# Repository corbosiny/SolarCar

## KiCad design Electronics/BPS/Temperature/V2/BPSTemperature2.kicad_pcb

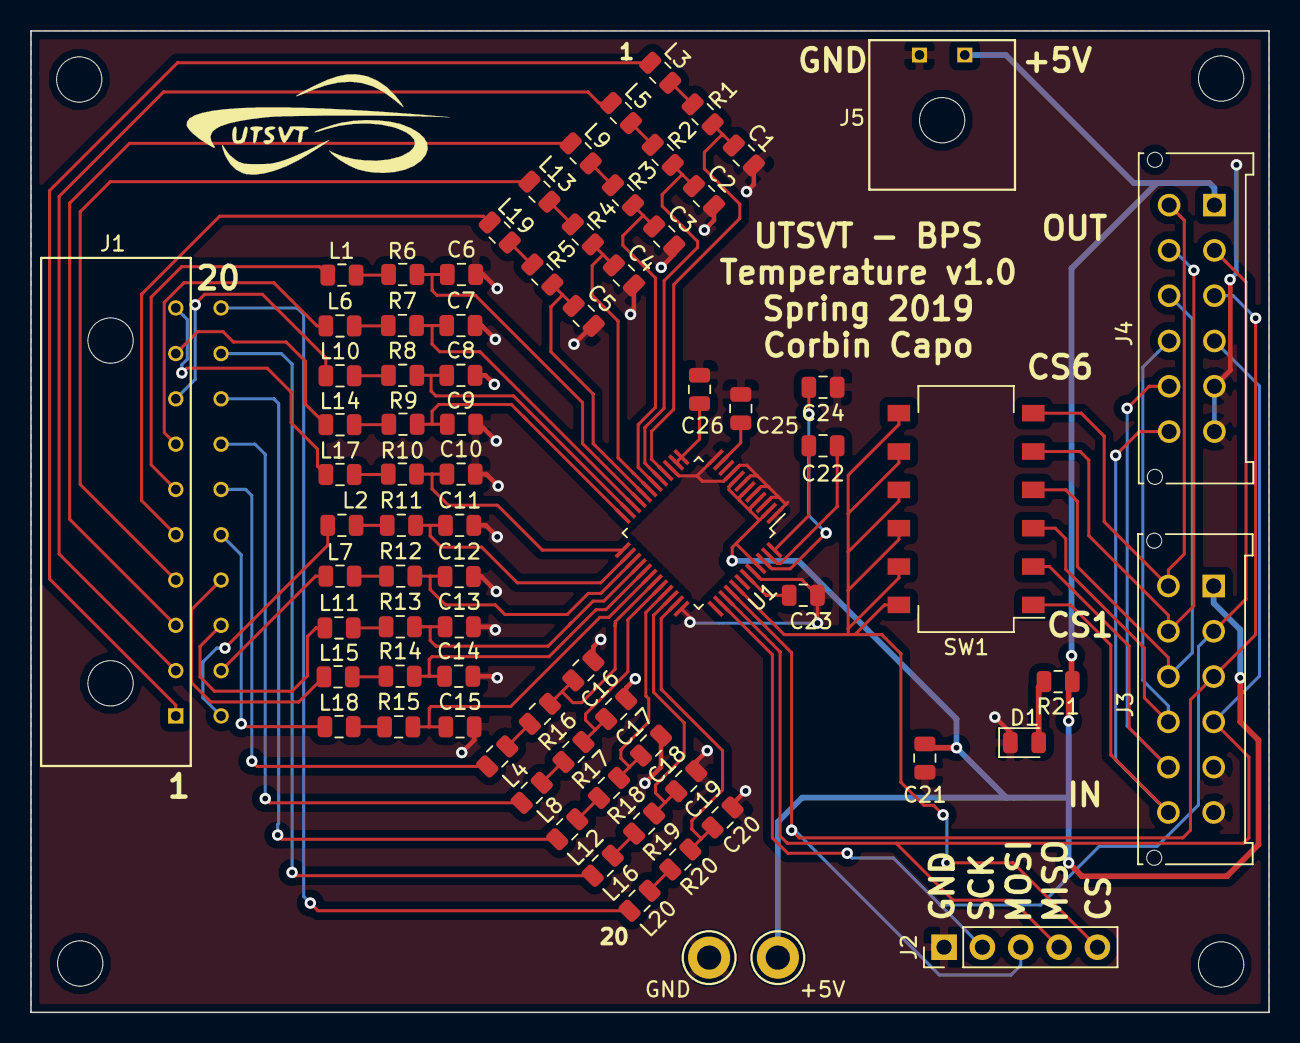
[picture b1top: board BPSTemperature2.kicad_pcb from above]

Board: 2 copper layers, 82.0 x 65.0 mm, 81 parts (0 on the bottom side), 79 nets.

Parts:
+5V: TestPoint; TestPoint_Keystone_5005-5009_Compact
C1, C2, C3, C4, C5, C6, C7, C8, C9, C10, C11, C12, C13, C14, C15, C16, C17, C18, C19, C20, C25, C26: 1uF; C_0805_2012Metric
C21: 0.1uF; C_0805_2012Metric
C22, C23, C24: 10uF; C_0805_2012Metric
D1: LED; LED_0805_2012Metric
GND: TestPoint; TestPoint_Keystone_5005-5009_Compact
J1: Conn_02x10_Counter_Clockwise; 02x10_Microfit_3.0_horizontal
J2: Logic Analyzer; PinHeader_1x05_P2.54mm_Vertical
J3, J4: Conn_02x06_Counter_Clockwise; Molex_MicroFit3.0_2x6xP3.00mm_PolarizingPeg_Vertical
J5: Conn_01x02; 43650-0202_01x02_Microfit 3.0_horizontal
L1, L2, L3, L4, L5, L6, L7, L8, L9, L10, L11, L12, L13, L14, L15, L16, L17, L18, L19, L20: Ferrite_Bead; L_0805_2012Metric
MH1, MH2, MH3, MH4: MountingHole; MountingHole_3mm
R1, R2, R3, R4, R5, R6, R7, R8, R9, R10, R11, R12, R13, R14, R15, R16, R17, R18, R19, R20: 1k; R_0805_2012Metric
R21: 1.55k; R_0805_2012Metric
SW1: SW_DIP_x06; SW_DIP_SPSTx06_Slide_Omron_A6S-610x_W8.9mm_P2.54mm
U1: LTC2983; LQFP-48_7x7mm_P0.5mm

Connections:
+5V: +5V.1, C21.2, J3.1, J4.1, J5.1, R21.1, U1.2, U1.4, U1.6, U1.8, U1.45
/CH1_LPF: J1.1, L3.2
/CH2_LPF: J1.2, L5.2
/CH3_LPF: J1.3, L9.2
/CH4_LPF: J1.4, L13.2
/CH5_LPF: J1.5, L19.2
/CH6_LPF: J1.6, L1.1
/CH7_LPF: J1.7, L6.1
/CH8_LPF: J1.8, L10.1
/CH9_LPF: J1.9, L14.1
/CH10_LPF: J1.10, L17.2
/CH11_LPF: J1.11, L2.1
/CH12_LPF: J1.12, L7.1
/CH13_LPF: J1.13, L11.1
/CH14_LPF: J1.14, L15.1
/CH15_LPF: J1.15, L18.1
/CH16_LPF: J1.16, L4.1
/CH17_LPF: J1.17, L8.1
/CH18_LPF: J1.18, L12.1
/CH19_LPF: J1.19, L16.1
/CH20_LPF: J1.20, L20.1
/CS1: J3.12, J4.12, SW1.1
/CS1_OUT: J2.5, SW1.7, SW1.8, SW1.9, SW1.10, SW1.11, SW1.12, U1.41
/CS2: J3.11, J4.11, SW1.2
/CS3: J3.10, J4.10, SW1.3
/CS4: J3.9, J4.9, SW1.4
/CS5: J3.8, J4.8, SW1.5
/CS6: J3.7, J4.7, SW1.6
/MISO: J2.4, J3.4, J4.4, U1.39
/MOSI: J2.3, J3.3, J4.3, U1.40
/SCK: J2.2, J3.2, J4.2, U1.38
GND: C1.2, C2.2, C3.2, C4.2, C5.2, C6.2, C7.2, C8.2, C9.2, C10.2, C11.2, C12.2, C13.2, C14.2, C15.2, C16.2, C17.2, C18.2, C19.2, C20.2, C21.1, C23.2, C24.2, C25.2, C26.2, D1.1, GND.1, J2.1, J3.5, J3.6, J4.5, J4.6, J5.2, U1.1, U1.3, U1.5, U1.7, U1.9, U1.12, U1.15, U1.36, U1.44
unnamed: C1.1, R1.2, U1.16
unnamed: C2.1, R2.2, U1.17
unnamed: C3.1, R3.2, U1.18
unnamed: C4.1, R4.2, U1.19
unnamed: C5.1, R5.2, U1.20
unnamed: C6.1, R6.2, U1.21
unnamed: C7.1, R7.2, U1.22
unnamed: C8.1, R8.2, U1.23
unnamed: C9.1, R9.2, U1.24
unnamed: C10.1, R10.2, U1.25
unnamed: C11.1, R11.2, U1.26
unnamed: C12.1, R12.2, U1.27
unnamed: C13.1, R13.2, U1.28
unnamed: C14.1, R14.2, U1.29
unnamed: C15.1, R15.2, U1.30
unnamed: C16.1, R16.2, U1.31
unnamed: C17.1, R17.2, U1.32
unnamed: C18.1, R18.2, U1.33
unnamed: C19.1, R19.2, U1.34
unnamed: C20.1, R20.2, U1.35
unnamed: C22.1, U1.48
unnamed: C22.2, U1.47
unnamed: C23.1, U1.43
unnamed: C24.1, U1.46
unnamed: C25.1, U1.11
unnamed: C26.1, U1.13, U1.14
unnamed: D1.2, R21.2
unnamed: L1.2, R6.1
unnamed: L2.2, R11.1
unnamed: L3.1, R1.1
unnamed: L4.2, R16.1
unnamed: L5.1, R2.1
unnamed: L6.2, R7.1
unnamed: L7.2, R12.1
unnamed: L8.2, R17.1
unnamed: L9.1, R3.1
unnamed: L10.2, R8.1
unnamed: L11.2, R13.1
unnamed: L12.2, R18.1
unnamed: L13.1, R4.1
unnamed: L14.2, R9.1
unnamed: L15.2, R14.1
unnamed: L16.2, R19.1
unnamed: L17.1, R10.1
unnamed: L18.2, R15.1
unnamed: L19.1, R5.1
unnamed: L20.2, R20.1

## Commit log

2018-09-03 Added gui code and modified serialMonitor to be compatible with it
2018-09-05 Adjusted commands to send to serialMonitor from the gui to match with mbed API for voltage/current
2018-09-05 *actual* Adjusted commands to send to serialMonitor from the gui to match with mbed API for voltage/current
2018-10-06 added ADC initialization and reading basics
2018-10-13 added ADC stuff
2018-10-15 Fixing threading stuff
2018-10-15 Thread working with refactored containers - not plots yet
2018-10-17 Refactored working for plots
2018-10-20 adding UART WriteInt function
2018-10-20 removed warning
2018-11-02 Changed baud rate and fixed leading whitespace issues
2018-11-02 Algo elements
2018-11-05 something something
2018-11-07 Full system demo
2018-11-14 Plot constants
2018-11-14 Working updating plot (one val)
2018-11-16 Started some refactoring
2018-11-17 Everything (or it seems) working with refactored code
2018-11-17 Working flask + qtapp simultaneous
2019-02-03 Interim change
2019-02-03 Chase why
2019-02-03 Added logos and references
2019-02-03 Hopefully final reference edit
2019-02-09 Updating branch
2019-02-09 New Debugger for BPS
2019-02-15 New connector for Temperature Board for BPS
